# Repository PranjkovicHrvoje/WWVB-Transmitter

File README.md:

# WWVB-Transmitter

WWVB transmitter made using SparkFun Pro Micro and Wemos D1 mini Lite.

Wemos D1 mini Lite connects to a WiFi network and retrieves the current time using NTP. It sends it to SparkFun Pro Micro which emmits the signal in the right format.

Pro Micro code is a modified version of https://github.com/micooke/WWVB.

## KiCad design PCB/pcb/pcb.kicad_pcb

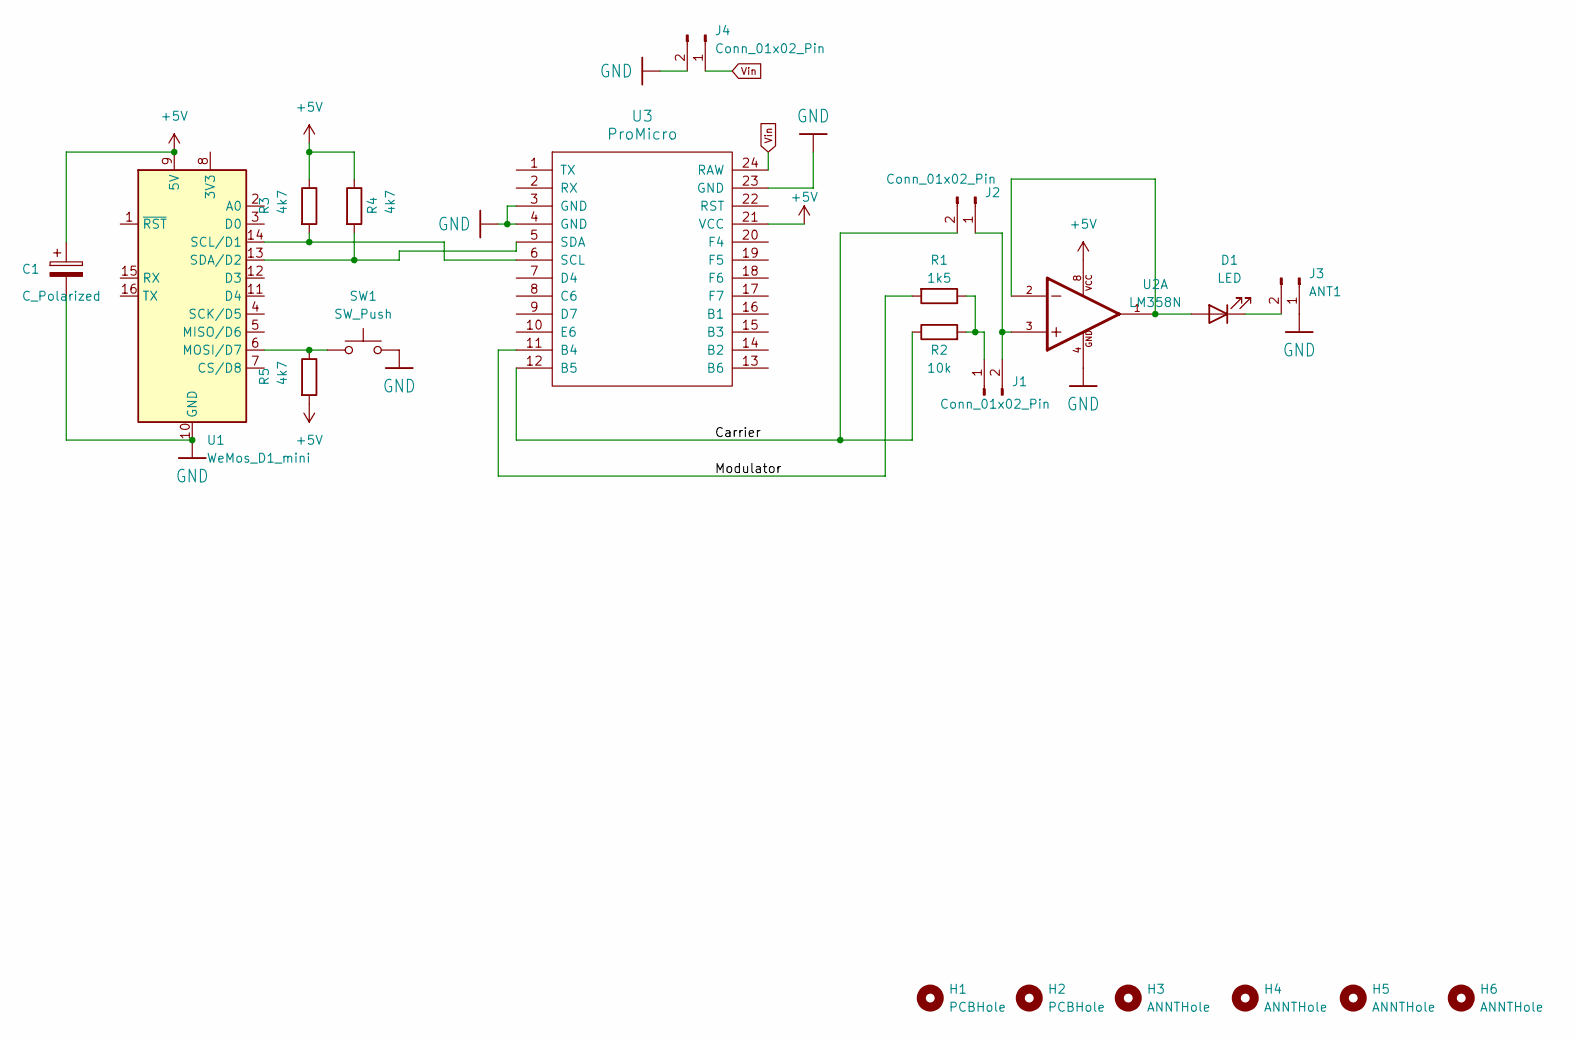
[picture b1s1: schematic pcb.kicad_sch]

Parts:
C1: C_Polarized; CP_EIA-3528-12_Kemet-T_Pad1.50x2.35mm_HandSolder
D1: LED; LED_D5.0mm
H1, H2: PCBHole; MountingHole_2.2mm_M2
H3, H4, H5, H6: ANNTHole; MountingHole_2.5mm
J1, J2, J4: Conn_01x02_Pin; PinHeader_1x02_P2.54mm_Vertical
J3: ANT1; PinHeader_1x02_P2.54mm_Vertical
R1: 1k5; R_0603_1608Metric
R2: 10k; R_0603_1608Metric
R3, R4, R5: 4k7; R_0603_1608Metric
SW1: SW_Push; SW_PUSH-12mm
U1: WeMos_D1_mini; WEMOS_D1_mini_light
U2: LM358N; DIP762W46P254L960H508Q8; PARTREV 1.0.3
U3: ProMicro

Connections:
+5V: C1.1, R3.1, R4.1, R5.2, U1.9 (5V), U2.8, U3.21 (VCC)
/Carrier: J2.2, R2.1, U3.12 (B5)
/Modulator: R1.2, U3.11 (B4)
GND: C1.2, J3.1, J4.2, SW1.2, U1.10 (GND), U2.4, U3.3 (GND), U3.4 (GND), U3.23 (GND)
unnamed: D1.2 (A), U2.1, U2.2
unnamed: D1.1 (K), J3.2
unnamed: J1.1, R1.1, R2.2
unnamed: J1.2, J2.1, U2.3
unnamed: R5.1, SW1.1, U1.6 (MOSI/D7)
unnamed: R3.2, U1.14 (SCL/D1), U3.6 (SCL)
unnamed: R4.2, U1.13 (SDA/D2), U3.5 (SDA)
Vin: J4.1, U3.24 (RAW)

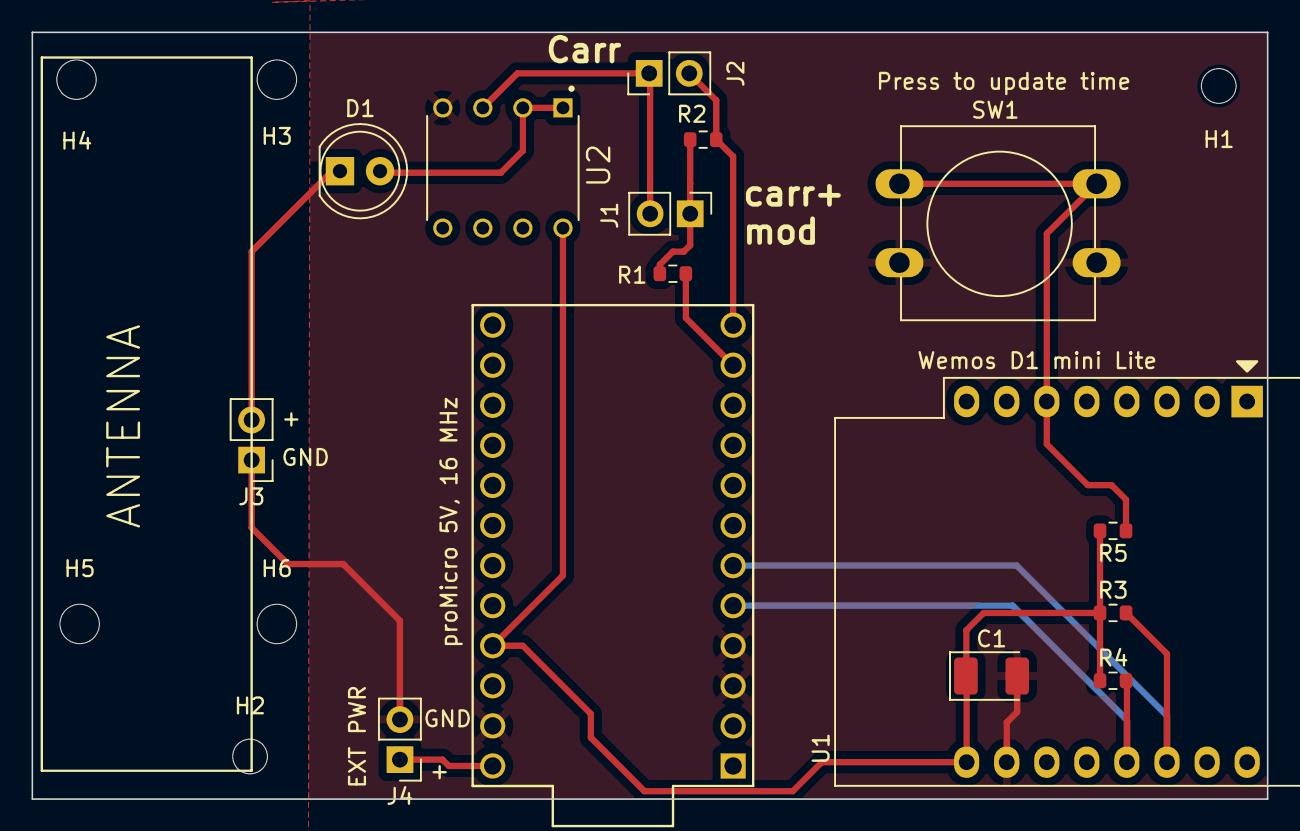
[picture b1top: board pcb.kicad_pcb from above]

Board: 2 copper layers, 78.3 x 48.6 mm, 21 parts (0 on the bottom side), 12 nets.

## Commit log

2023-03-21 Add files via upload
    WEMOS files used for connecting to internet and getting time
2023-03-21 Enabled connecting to internet and getting time
    WEMOS code used for connecting to internet and getting time
2023-05-04 Fixed time formating
2023-05-04 requires aditional optimisation
2023-05-04 requires further optimisation
2023-05-10 Fixed grabbing time
2023-05-10 Removed Wi-Fi credentials
